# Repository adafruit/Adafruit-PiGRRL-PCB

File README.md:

## Adafruit PiGRRL PCBs

<a href="http://www.adafruit.com/products/3015">&nbsp; 
<a href="http://www.adafruit.com/products/2934"><br/>
Click a picture to purchase from the Adafruit shop</a>

PCB files for the PiGrrl Gamepads. Format is EagleCAD schematic and board layout

For more details, check out the product pages at
  * PiGRRL 2.0 Custom Gamepad PCB http://www.adafruit.com/products/3015
  * PiGrrl Zero Custom Gamepad PCB http://www.adafruit.com/products/2934

### Description

**PiGrrl 2:** This is the Custom Gamepad PCB for the PiGRRL 2 pack! The board is designed for use in portable gaming projects like the PiGRRL 2 but it's basically everything-you-need to make your very own DIY gaming project with GPIO input

We've dramatically cut the build time in half of the PiGRRL 2 pack by making this custom gamepad PCB. Just solder in 6mm tactile switch buttons and an 2x20 header or IDC box header to the gamepad PCB - No more tedious button wiring!

Comes with just the PCB! Best for people who already have the rest of the parts, or are doing a custom build.

**PiGrrl Zero:** This is the custom Gamepad PCB for the PiGRRL Zero Parts Kit! 

We've dramatically cut the build time in half of the PiGRRL Zero pack by making this custom gamepad PCB. Just solder in 6mm tactile switch buttons and do a some wiring from the header pins on the PCB.

Comes with just a single PCB and you'll need 2 to finish the project! Best for people who already have the rest of the parts, or are doing a custom build.

### License

Adafruit invests time and resources providing this open source design, please support Adafruit and open-source hardware by purchasing products from [Adafruit](https://www.adafruit.com)!

Designed by Limor Fried/Ladyada for Adafruit Industries.

Creative Commons Attribution/Share-Alike, all text above must be included in any redistribution. See license.txt for additional details.

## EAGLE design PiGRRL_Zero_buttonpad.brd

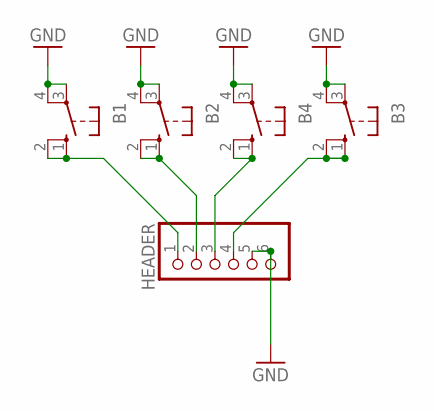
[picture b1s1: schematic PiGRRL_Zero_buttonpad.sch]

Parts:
B1, B2, B3, B4: 10-XX; B3F-10XX
HEADER: PINHD-1X6; 1X06

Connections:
GND: B1.3, B1.4 (P1), B2.3, B2.4 (P1), B3.3, B3.4 (P1), B4.3, B4.4 (P1), HEADER.5, HEADER.6
unnamed: B1.1 (S), B1.2 (S1), HEADER.1
unnamed: B2.1 (S), B2.2 (S1), HEADER.2
unnamed: B3.1 (S), B3.2 (S1), HEADER.4
unnamed: B4.1 (S), B4.2 (S1), HEADER.3

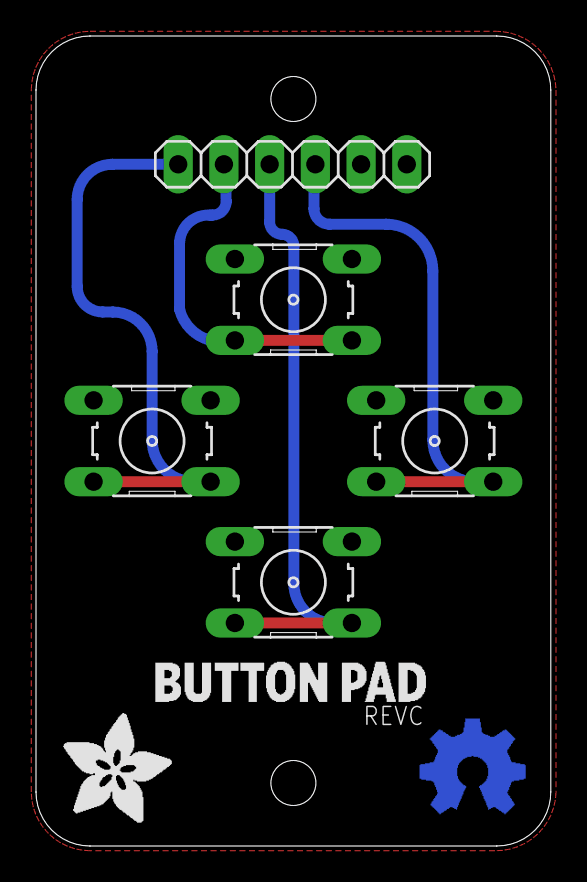
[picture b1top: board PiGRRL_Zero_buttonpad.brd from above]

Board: 2 copper layers, 28.6 x 45.0 mm, 5 parts (0 on the bottom side), 5 nets.

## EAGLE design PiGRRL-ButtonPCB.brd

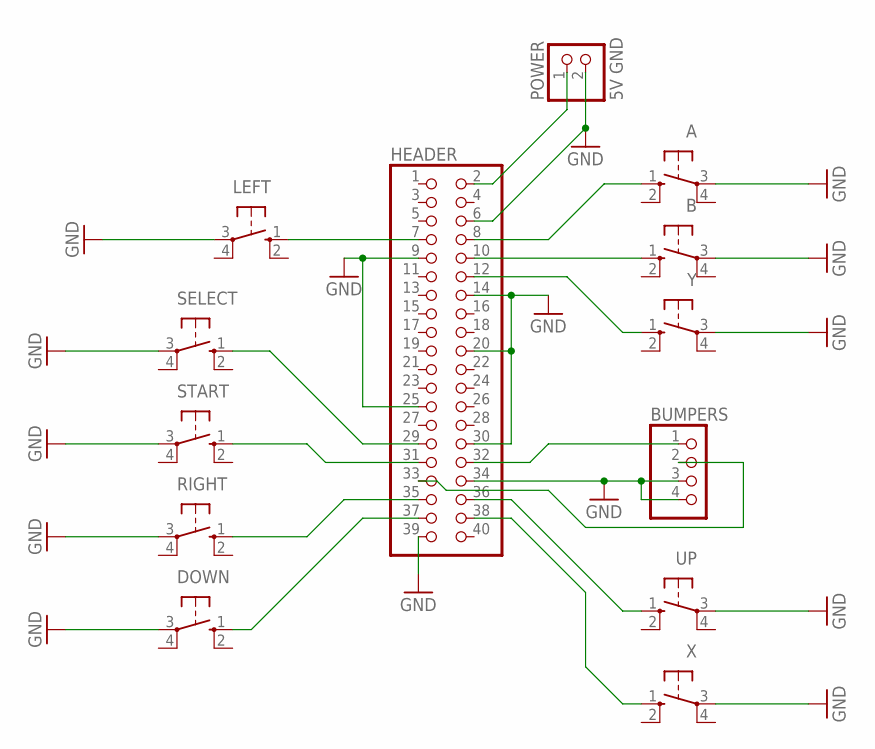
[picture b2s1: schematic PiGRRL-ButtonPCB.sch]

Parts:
A: 10-XX; B3F-10XX
B: 10-XX; B3F-10XX
BUMPERS: PINHD-1X4; 1X04
DOWN: 10-XX; B3F-10XX
HEADER: PINHD-2X20; 2X20
LEFT: 10-XX; B3F-10XX
POWER: 5V GND; 1X02
RIGHT: 10-XX; B3F-10XX
SELECT: 10-XX; B3F-10XX
START: 10-XX; B3F-10XX
UP: 10-XX; B3F-10XX
X: 10-XX; B3F-10XX
Y: 10-XX; B3F-10XX

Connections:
+5V: HEADER.2, POWER.1
GND: A.3, B.3, BUMPERS.3, BUMPERS.4, DOWN.3, HEADER.6, HEADER.9, HEADER.14, HEADER.20, HEADER.25, HEADER.30, HEADER.34, HEADER.39, LEFT.3, POWER.2, RIGHT.3, SELECT.3, START.3, UP.3, X.3, Y.3
unnamed: HEADER.7, LEFT.1 (S)
unnamed: HEADER.36, UP.1 (S)
unnamed: HEADER.12, Y.1 (S)
unnamed: HEADER.35, RIGHT.1 (S)
unnamed: DOWN.1 (S), HEADER.37
unnamed: HEADER.38, X.1 (S)
unnamed: A.1 (S), HEADER.8
unnamed: B.1 (S), HEADER.10
unnamed: HEADER.29, SELECT.1 (S)
unnamed: HEADER.31, START.1 (S)
unnamed: BUMPERS.1, HEADER.32
unnamed: BUMPERS.2, HEADER.33

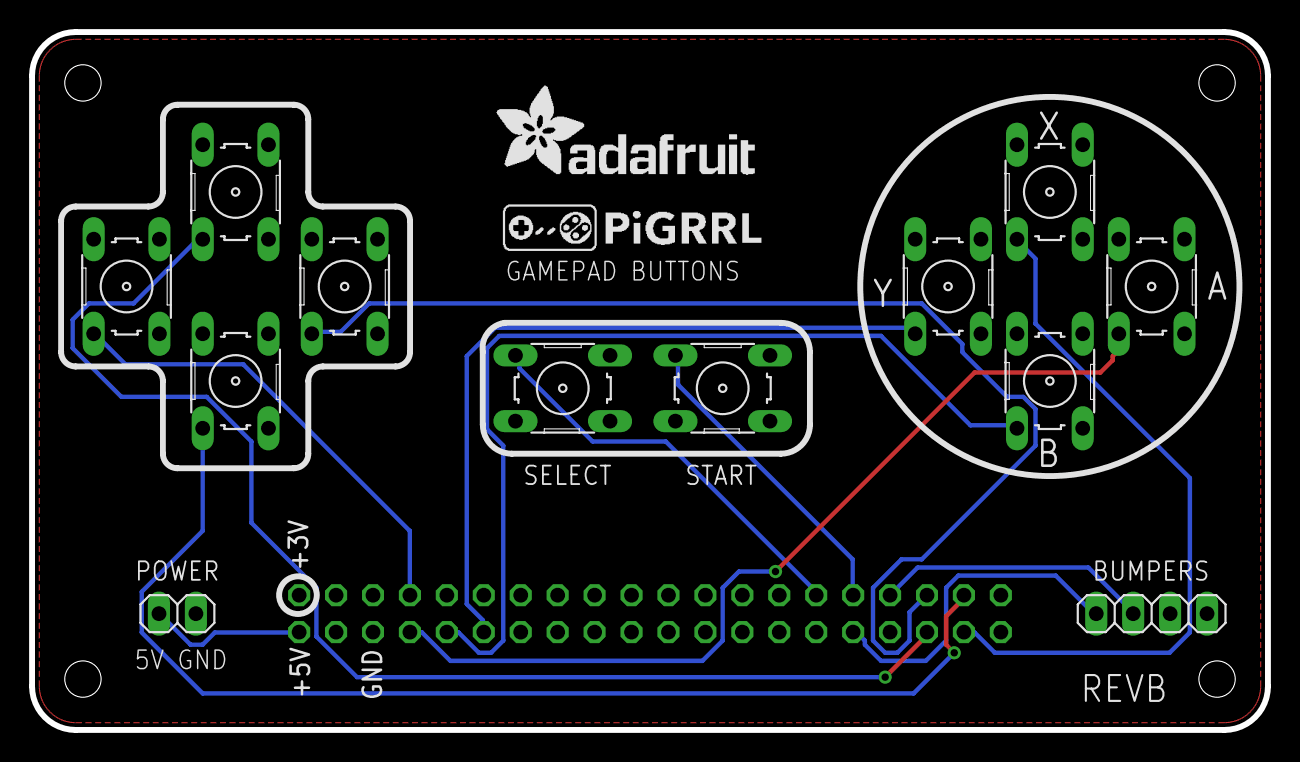
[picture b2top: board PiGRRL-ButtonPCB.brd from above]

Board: 2 copper layers, 85.0 x 48.0 mm, 13 parts (1 on the bottom side), 14 nets.

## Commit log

2017-09-25 both zero and 'pi 3' based
